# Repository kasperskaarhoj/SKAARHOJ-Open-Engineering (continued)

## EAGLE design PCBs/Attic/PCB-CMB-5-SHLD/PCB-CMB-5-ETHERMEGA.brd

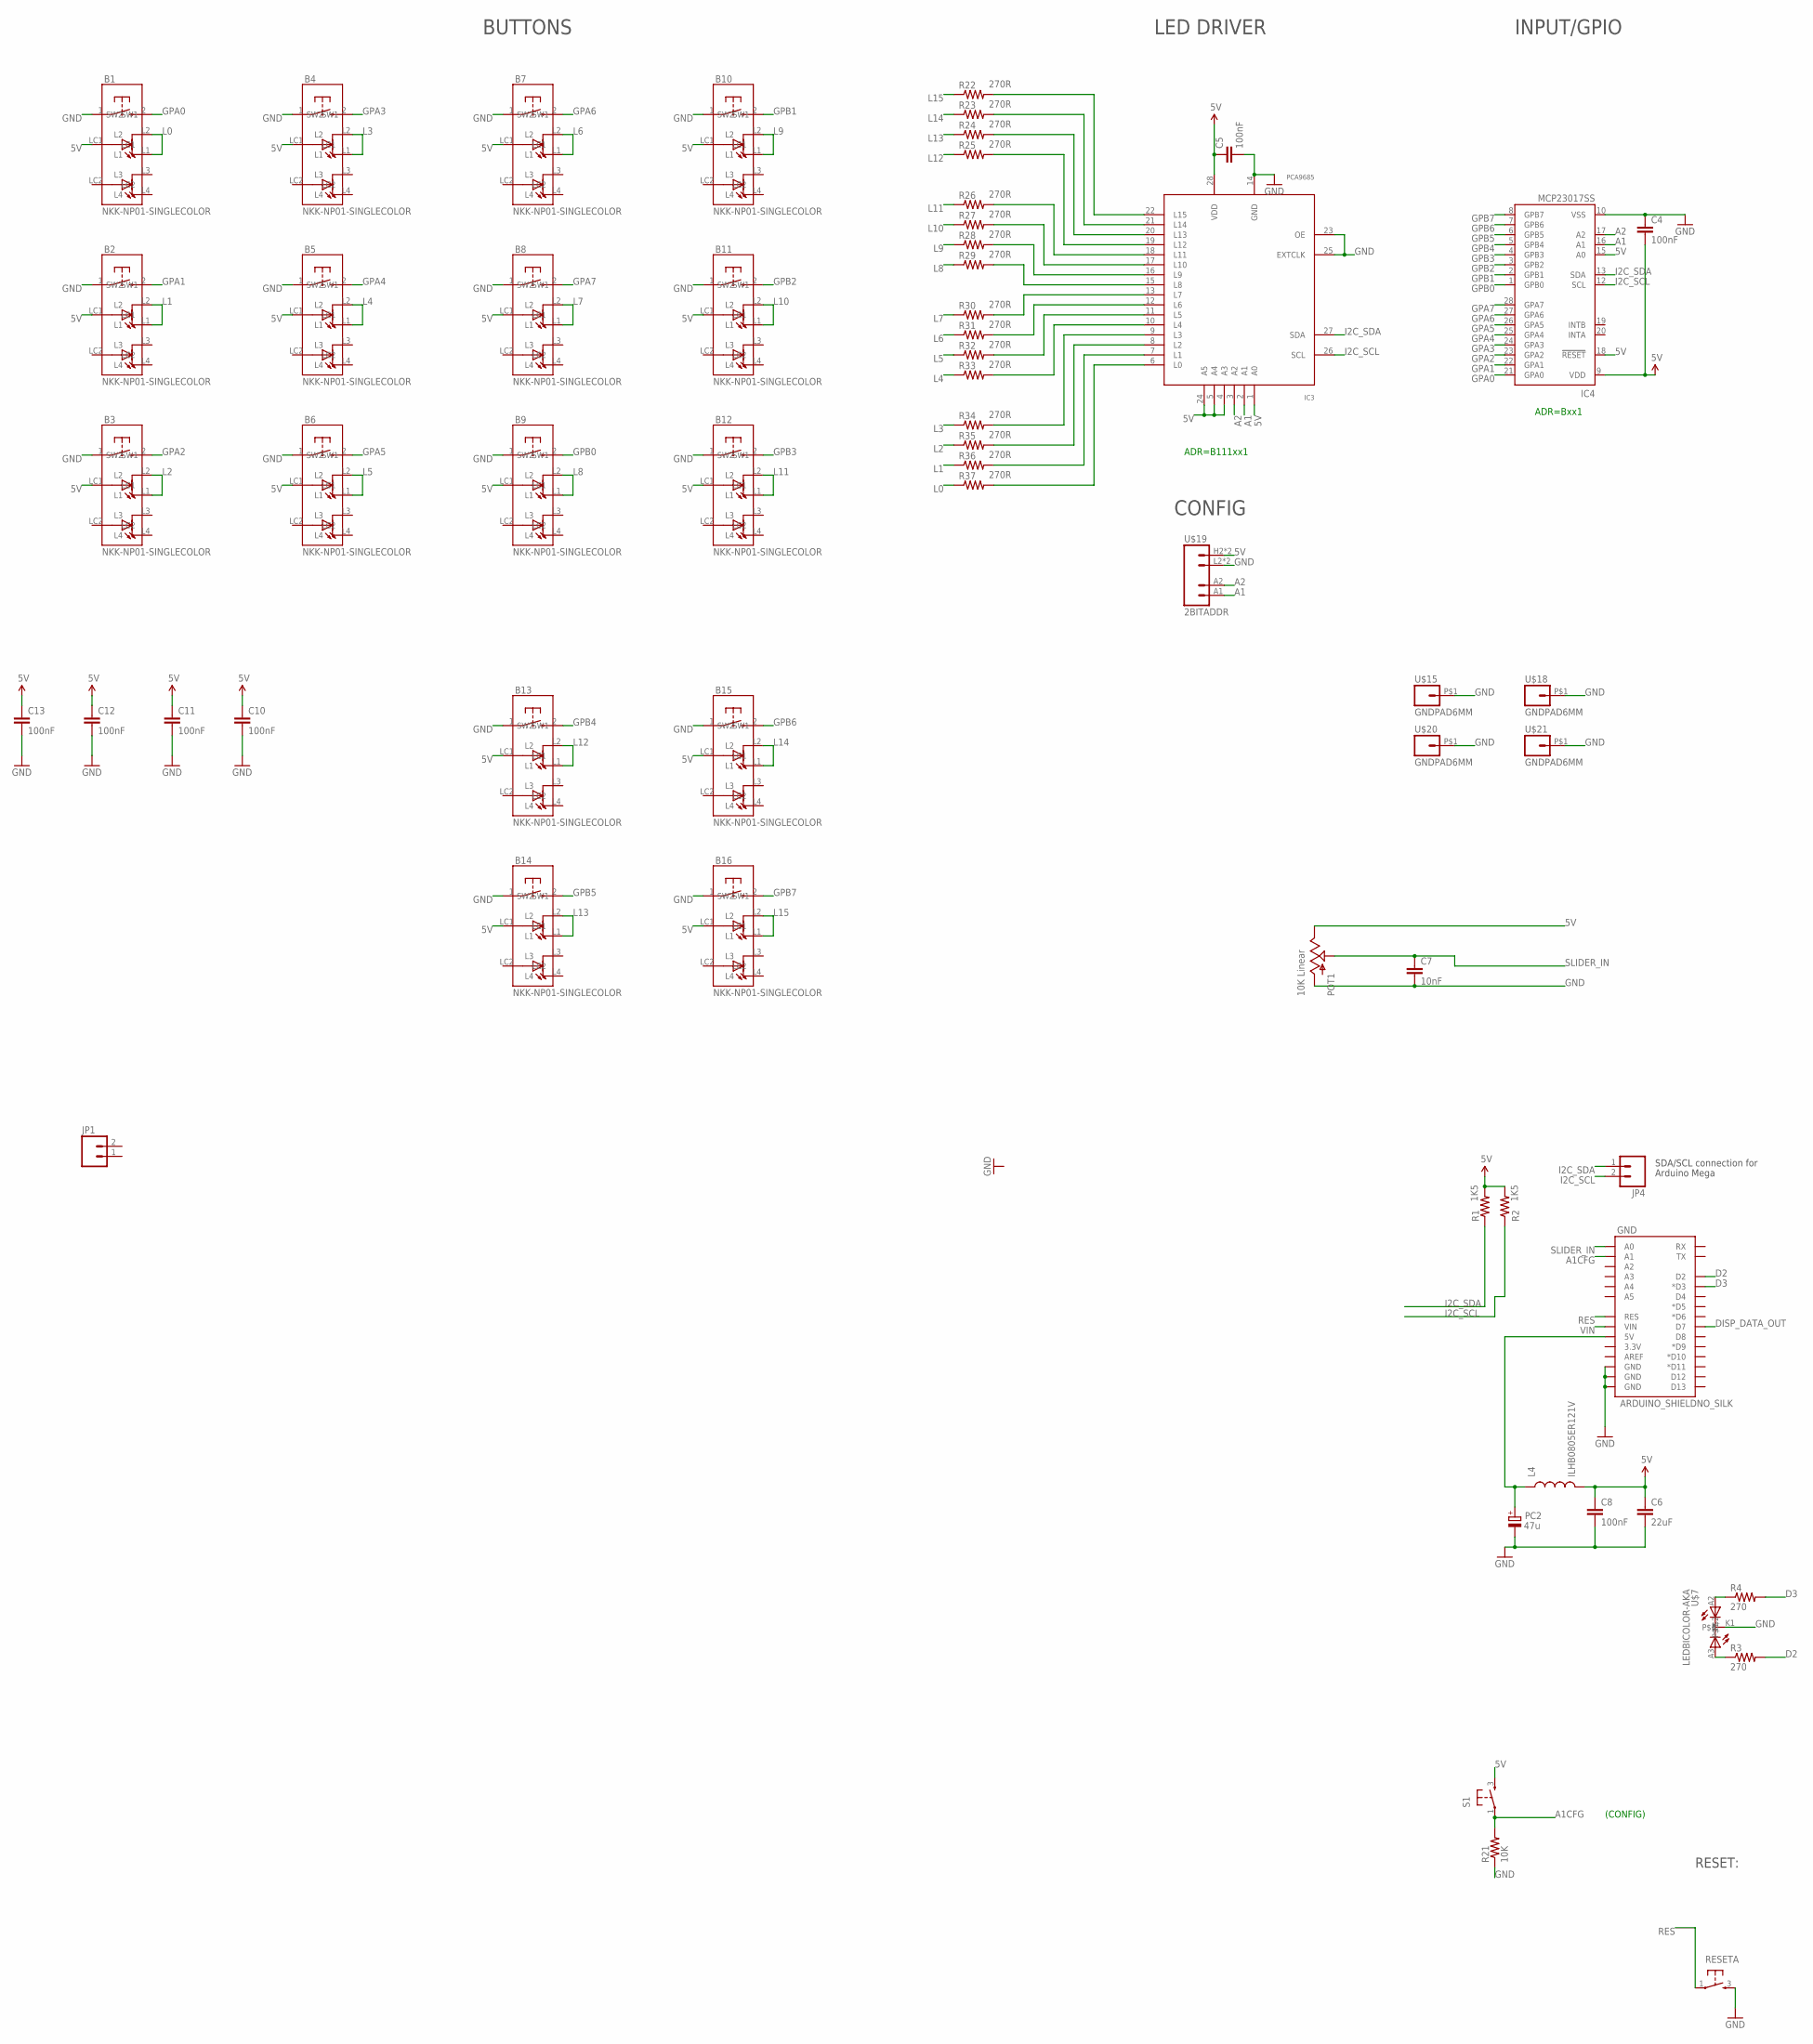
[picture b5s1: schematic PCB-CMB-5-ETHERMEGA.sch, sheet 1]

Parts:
B1, B2, B3, B4, B5, B6, B7, B8, B9, B10, B11, B12, B13, B14, B15, B16: NKK-NP01-SINGLECOLOR; NKK-NP01
C4, C5, C8, C10, C11, C12, C13: 100nF; 0603-CAP
C6: 22uF; 0805
C7: 10nF; 0603-CAP
GND: ARDUINO_SHIELDNO_SILK; DUEMILANOVE_VIAS
IC3: PCA9685; TSSOP28
IC4: MCP23017SS; SSOP28; MPN MCP23017-E/SS
JP1, JP4: M02PTH; 1X02
L4: ILHB0805ER121V; 0805
PC2: 47u; PANASONIC_D
POT1: 10K Linear; SLIDER20
R1, R2: 1K5; 0603-RES
R3, R4: 270; 0603-RES
R21: 10K; 0603-RES
R22, R23, R24, R25, R26, R27, R28, R29, R30, R31, R32, R33, R34, R35, R36, R37: 270R; 0603-RES
RESETA: TAC_SWITCH; PUSHBUTTON
S1: TAC_SWITCH; PUSHBUTTON
U$7: LEDBICOLOR-AKA; LED5MM-BICOLOR
U$15, U$18, U$20, U$21: GNDPAD6MM; 3.2MMPAD6MM
U$19: 2BITADDR

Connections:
5V: B1.LC1, B2.LC1, B3.LC1, B4.LC1, B5.LC1, B6.LC1, B7.LC1, B8.LC1, B9.LC1, B10.LC1, B11.LC1, B12.LC1, B13.LC1, B14.LC1, B15.LC1, B16.LC1, C4.2, C5.1, C6.1, C8.1, C10.1, C11.1, C12.1, C13.1, IC3.1 (A0), IC3.4 (A3), IC3.5 (A4), IC3.24 (A5), IC3.28 (VDD), IC4.9 (VDD), IC4.15 (A0), IC4.18 (!RESET), L4.2, POT1.1 (E), R1.2, R2.2, S1.3, U$19.H2 (VCC), U$19.H3 (VCC)
A1: IC3.2 (A1), IC4.16 (A1), U$19.A1
A1CFG: GND.A1, R21.2, S1.1
A2: IC3.3 (A2), IC4.17 (A2), U$19.A2
ARD_5V: GND.5V, L4.1, PC2.+
D2: GND.D2, R3.2
D3: GND.D3 (*D3), R4.2
DISP_DATA_OUT: GND.D7
GND: B1.1 (SW1), B2.1 (SW1), B3.1 (SW1), B4.1 (SW1), B5.1 (SW1), B6.1 (SW1), B7.1 (SW1), B8.1 (SW1), B9.1 (SW1), B10.1 (SW1), B11.1 (SW1), B12.1 (SW1), B13.1 (SW1), B14.1 (SW1), B15.1 (SW1), B16.1 (SW1), C4.1, C5.2, C6.2, C7.2, C8.2, C10.2, C11.2, C12.2, C13.2, GND.GND@0 (GND), GND.GND@1 (GND), GND.GND@2 (GND), IC3.14 (GND), IC3.23 (OE), IC3.25 (EXTCLK), IC4.10 (VSS), PC2.-, POT1.3 (A), R21.1, RESETA.3, U$7.K1, U$15.P$1, U$18.P$1, U$19.L2 (GND), U$19.L3 (GND), U$20.P$1, U$21.P$1
GPA0: B1.2 (SW2), IC4.21 (GPA0)
GPA1: B2.2 (SW2), IC4.22 (GPA1)
GPA2: B3.2 (SW2), IC4.23 (GPA2)
GPA3: B4.2 (SW2), IC4.24 (GPA3)
GPA4: B5.2 (SW2), IC4.25 (GPA4)
GPA5: B6.2 (SW2), IC4.26 (GPA5)
GPA6: B7.2 (SW2), IC4.27 (GPA6)
GPA7: B8.2 (SW2), IC4.28 (GPA7)
GPB0: B9.2 (SW2), IC4.1 (GPB0)
GPB1: B10.2 (SW2), IC4.2 (GPB1)
GPB2: B11.2 (SW2), IC4.3 (GPB2)
GPB3: B12.2 (SW2), IC4.4 (GPB3)
GPB4: B13.2 (SW2), IC4.5 (GPB4)
GPB5: B14.2 (SW2), IC4.6 (GPB5)
GPB6: B15.2 (SW2), IC4.7 (GPB6)
GPB7: B16.2 (SW2), IC4.8 (GPB7)
I2C_SCL: IC3.26 (SCL), IC4.12 (SCL), JP4.2, R2.1
I2C_SDA: IC3.27 (SDA), IC4.13 (SDA), JP4.1, R1.1
L0: B1.L1, B1.L2, R37.1
L1: B2.L1, B2.L2, R36.1
L2: B3.L1, B3.L2, R35.1
L3: B4.L1, B4.L2, R34.1
L4: B5.L1, B5.L2, R33.1
L5: B6.L1, B6.L2, R32.1
L6: B7.L1, B7.L2, R31.1
L7: B8.L1, B8.L2, R30.1
L8: B9.L1, B9.L2, R29.1
L9: B10.L1, B10.L2, R28.1
L10: B11.L1, B11.L2, R27.1
L11: B12.L1, B12.L2, R26.1
L12: B13.L1, B13.L2, R25.1
L13: B14.L1, B14.L2, R24.1
L14: B15.L1, B15.L2, R23.1
L15: B16.L1, B16.L2, R22.1
unnamed: IC3.13 (L7), R30.2
unnamed: R4.1, U$7.A2
unnamed: R3.1, U$7.A3
unnamed: IC3.12 (L6), R31.2
unnamed: IC3.11 (L5), R32.2
unnamed: IC3.10 (L4), R33.2
unnamed: IC3.9 (L3), R34.2
unnamed: IC3.8 (L2), R35.2
unnamed: IC3.7 (L1), R36.2
unnamed: IC3.6 (L0), R37.2
unnamed: IC3.15 (L8), R29.2
unnamed: IC3.16 (L9), R28.2
unnamed: IC3.17 (L10), R27.2
unnamed: IC3.18 (L11), R26.2
unnamed: IC3.19 (L12), R25.2
unnamed: IC3.20 (L13), R24.2
unnamed: IC3.21 (L14), R23.2
unnamed: IC3.22 (L15), R22.2
RES: GND.RES, RESETA.1
SLIDER_IN: C7.1, GND.A0, POT1.2A (S)
VIN: GND.VIN

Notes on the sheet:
SDA/SCL connection for
Arduino Mega
(CONFIG)
ADR=B111xx1
ADR=Bxx1
BUTTONS
LED DRIVER
INPUT/GPIO
CONFIG
RESET:

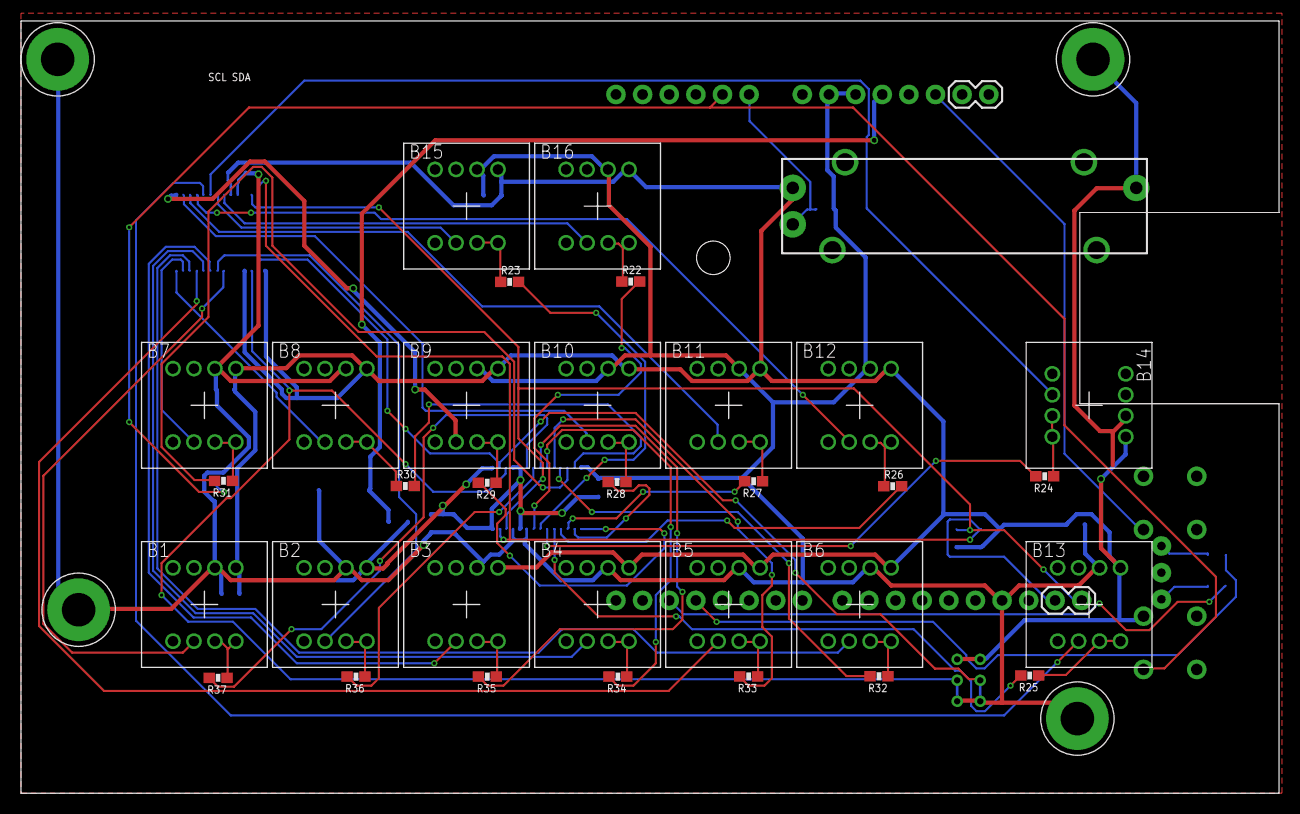
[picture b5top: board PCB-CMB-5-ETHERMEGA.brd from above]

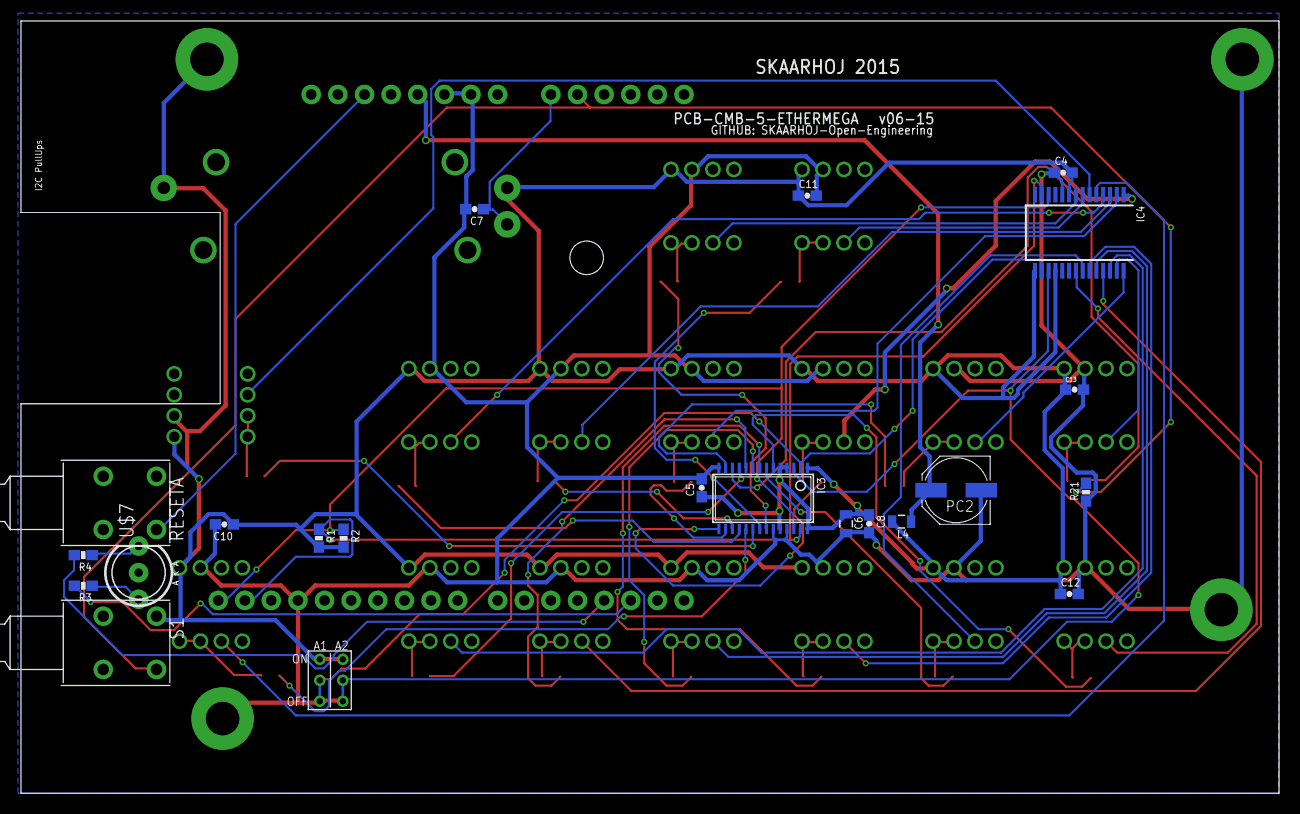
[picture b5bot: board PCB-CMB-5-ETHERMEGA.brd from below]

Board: 2 copper layers, 120.0 x 73.7 mm, 62 parts (22 on the bottom side), 62 nets.
